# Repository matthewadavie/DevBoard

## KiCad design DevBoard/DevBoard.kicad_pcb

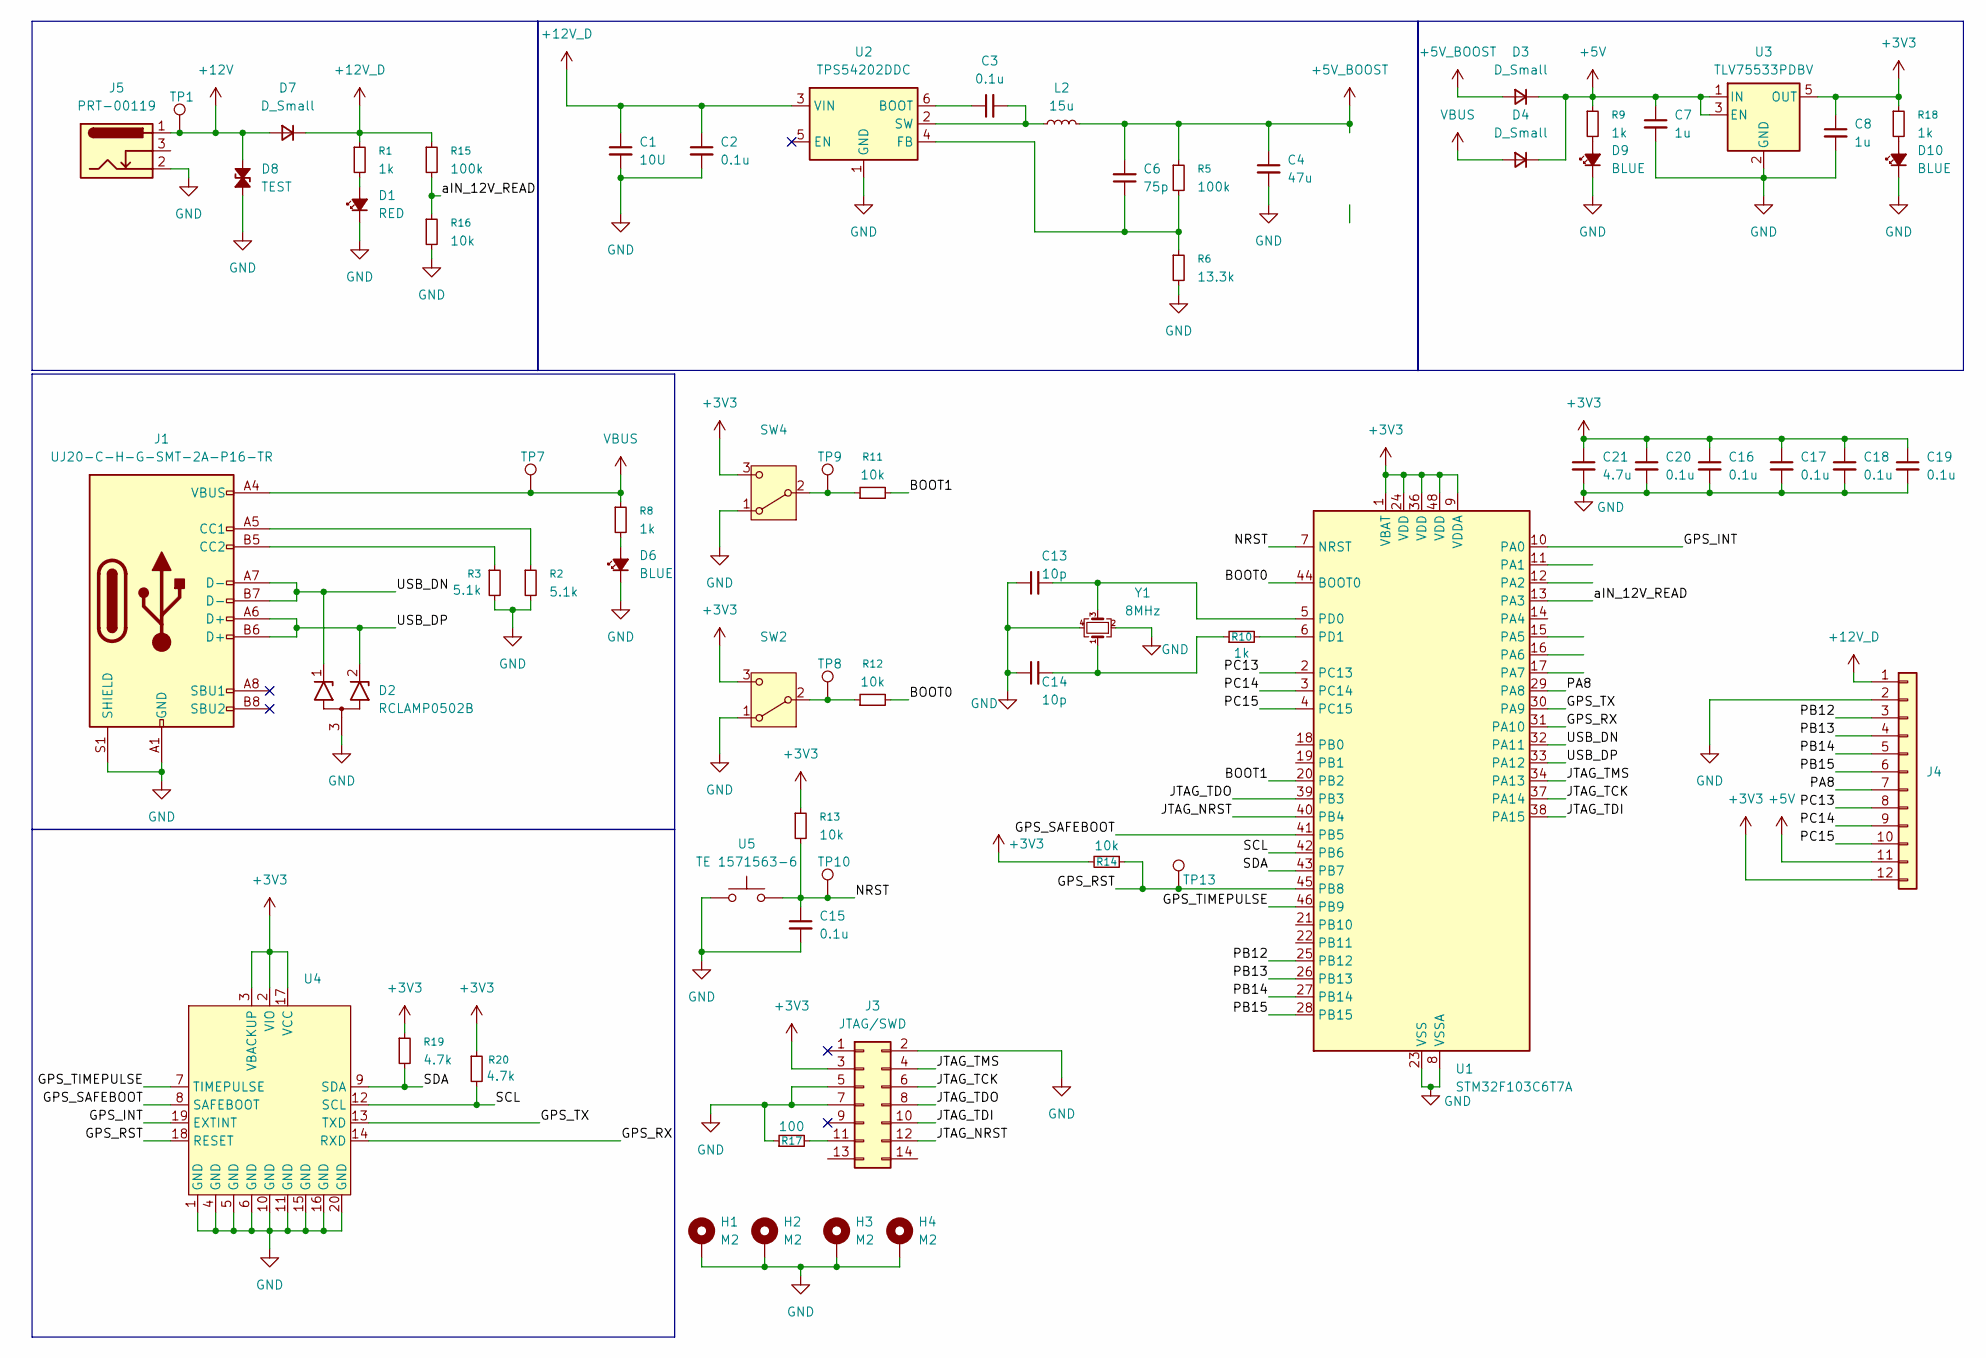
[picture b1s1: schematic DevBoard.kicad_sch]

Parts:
C1: 10U; C_0805_2012Metric_Pad1.18x1.45mm_HandSolder
C2, C3, C15, C16, C17, C18, C19, C20: 0.1u; C_0603_1608Metric_Pad1.08x0.95mm_HandSolder
C4: 47u; C_0805_2012Metric_Pad1.18x1.45mm_HandSolder
C6: 75p; C_0603_1608Metric_Pad1.08x0.95mm_HandSolder
C7, C8: 1u; C_0805_2012Metric_Pad1.18x1.45mm_HandSolder
C13, C14: 10p; C_0603_1608Metric_Pad1.08x0.95mm_HandSolder
C21: 4.7u; C_0805_2012Metric_Pad1.18x1.45mm_HandSolder
D1: RED; LED_0603_1608Metric_Pad1.05x0.95mm_HandSolder
D2: RCLAMP0502B; SOT-416
D3, D4, D7: D_Small; D_0805_2012Metric_Pad1.15x1.40mm_HandSolder
D6, D9, D10: BLUE; LED_0603_1608Metric_Pad1.05x0.95mm_HandSolder
D8: TEST
H1, H2, H3, H4: M2; MountingHole_2.2mm_M2_ISO7380_Pad_TopBottom
J1: UJ20-C-H-G-SMT-2A-P16-TR; MPN UJ20-C-H-G-SMT-2A-P16-TR; Mouser SPN 179-CHGSMT2AP16TR
J3: JTAG/SWD; PinHeader_2x07_P1.27mm_Vertical_SMD
J4: Conn_01x12; PinHeader_1x12_P2.54mm_Vertical
J5: PRT-00119; BarrelJack_3Pin_PJ202A; MPN PRT-00119; Mouser SPN 474-PRT-00119
L2: 15u; L_Coilcraft_XAL40; MPN XAL4040-153MEC; Mouser SPN 994-XAL4040-153MEC
R1, R8, R9, R18: 1k; R_0603_1608Metric_Pad0.98x0.95mm_HandSolder
R2, R3: 5.1k; R_0603_1608Metric_Pad0.98x0.95mm_HandSolder
R5, R15: 100k; R_0603_1608Metric_Pad0.98x0.95mm_HandSolder
R6: 13.3k; R_0603_1608Metric_Pad0.98x0.95mm_HandSolder
R10: 1k; R_0402_1005Metric_Pad0.72x0.64mm_HandSolder
R11, R12, R13, R14, R16: 10k; R_0603_1608Metric_Pad0.98x0.95mm_HandSolder
R17: 100; R_0603_1608Metric_Pad0.98x0.95mm_HandSolder
R19, R20: 4.7k; R_0603_1608Metric_Pad0.98x0.95mm_HandSolder
SW2, SW4: SLW-88229-2-SMT-TR; MPN SLW-88229-2-SMT-TR; Mouser SPN 179-SLW-88229-2SMTTR
TP1, TP7, TP8, TP9, TP10, TP13: TestPoint; TestPoint_Pad_D1.0mm
U1: STM32F103C6T7A; LQFP-48_7x7mm_P0.5mm; MPN STM32F103C6T7A; Mouser SPN 511-STM32F103C6T7A
U2: TPS54202DDC; SOT-23-6
U3: TLV75533PDBV; SOT-23-5
U4: SAM-M10Q
U5: TE 1571563-6; 506-1571563-6; MPN 1571563-6; Mouser SPN 506-1571563-6
Y1: 8MHz; Crystal_FC3BA; MPN FC3BAEBDI8.0-T1; Mouser SPN 815-FC3BAEBDI8.0-T1

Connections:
+3V3: C8.1, C16.1, C17.1, C18.1, C19.1, C20.1, C21.1, J3.3, J4.12, R13.1, R14.2, R18.1, R19.1, R20.1, SW2.3 (C), SW4.3 (C), U1.1 (VBAT), U1.9 (VDDA), U1.24 (VDD), U1.36 (VDD), U1.48 (VDD), U3.5 (OUT), U4.2 (VIO), U4.3 (VBACKUP), U4.17 (VCC); also elsewhere on the board
+5V: C7.1, D3.1 (K), D4.1 (K), J4.11, R9.1, U3.1 (IN), U3.3 (EN)
+5V_BOOST: C4.1, C6.2, D3.2 (A), L2.2, R5.1
+12V: D7.2 (A), D8.2 (A2), J5.1, TP1.1
+12V_D: C1.1, C2.1, D7.1 (K), J4.1, R1.1, R15.1, U2.3 (VIN)
/BOOT0: R12.2, U1.44 (BOOT0)
/BOOT1: R11.2, U1.20 (PB2)
/GPS_INT: U1.10 (PA0), U4.19 (EXTINT)
/GPS_RST: R14.1, TP13.1, U1.45 (PB8), U4.18 (RESET)
/GPS_RX: U1.31 (PA10), U4.14 (RXD)
/GPS_SAFEBOOT: U1.41 (PB5), U4.8 (SAFEBOOT)
/GPS_TIMEPULSE: U1.46 (PB9), U4.7 (TIMEPULSE)
/GPS_TX: U1.30 (PA9), U4.13 (TXD)
/JTAG_NRST: J3.12, U1.40 (PB4)
/JTAG_TCK: J3.6, U1.37 (PA14)
/JTAG_TDI: J3.10, U1.38 (PA15)
/JTAG_TDO: J3.8, U1.39 (PB3)
/JTAG_TMS: J3.4, U1.34 (PA13)
/NRST: C15.1, R13.2, TP10.1, U1.7 (NRST), U5.2
/PA8: J4.7, U1.29 (PA8)
/PB12: J4.3, U1.25 (PB12)
/PB13: J4.4, U1.26 (PB13)
/PB14: J4.5, U1.27 (PB14)
/PB15: J4.6, U1.28 (PB15)
/PC13: J4.8, U1.2 (PC13)
/PC14: J4.9, U1.3 (PC14)
/PC15: J4.10, U1.4 (PC15)
/SCL: R20.2, U1.42 (PB6), U4.12 (SCL)
/SDA: R19.2, U1.43 (PB7), U4.9 (SDA)
/USB_DN: D2.1 (K1), J1.A7 (D-), J1.B7 (D-), U1.32 (PA11)
/USB_DP: D2.2 (K2), J1.A6 (D+), J1.B6 (D+), U1.33 (PA12)
/aIN_12V_READ: R15.2, R16.1, U1.13 (PA3)
GND: C1.2, C2.2, C4.2, C7.2, C8.2, C13.1, C14.1, C15.2, C16.2, C17.2, C18.2, C19.2, C20.2, C21.2, D1.1 (K), D2.3 (A), D6.1 (K), D8.1 (A1), D9.1 (K), D10.1 (K), H1.1, H2.1, H3.1, H4.1, J1.A1 (GND), J1.A12 (GND), J1.B1 (GND), J1.B12 (GND), J1.S1 (SHIELD), J3.2, J3.5, J3.7, J4.2, J5.2, R2.2, R3.2, R6.2, R16.2, R17.1, SW2.1 (A), SW4.1 (A), U1.8 (VSSA), U1.23 (VSS), U1.35 (VSS), U1.47 (VSS), U2.1 (GND), U3.2 (GND), U4.1 (GND), U4.4 (GND), U4.5 (GND), U4.6 (GND), U4.10 (GND), U4.11 (GND), U4.15 (GND), U4.16 (GND), U4.20 (GND), U5.1, Y1.2, Y1.4
unnamed: C14.2, R10.1, Y1.1
unnamed: D1.2 (A), R1.2
unnamed: D6.2 (A), R8.2
unnamed: D9.2 (A), R9.2
unnamed: D10.2 (A), R18.2
unnamed: J1.A5 (CC1), R2.1
unnamed: J1.B5 (CC2), R3.1
unnamed: J3.11, R17.2
unnamed: R12.1, SW2.2 (B), TP8.1
unnamed: R11.1, SW4.2 (B), TP9.1
unnamed: C13.2, U1.5 (PD0), Y1.3
unnamed: R10.2, U1.6 (PD1)
unnamed: C3.1, U2.6 (BOOT)
unnamed: C6.1, R5.2, R6.1, U2.4 (FB)
unnamed: C3.2, L2.1, U2.2 (SW)
VBUS: D4.2 (A), J1.A4 (VBUS), J1.A9 (VBUS), J1.B4 (VBUS), J1.B9 (VBUS), R8.1, TP7.1

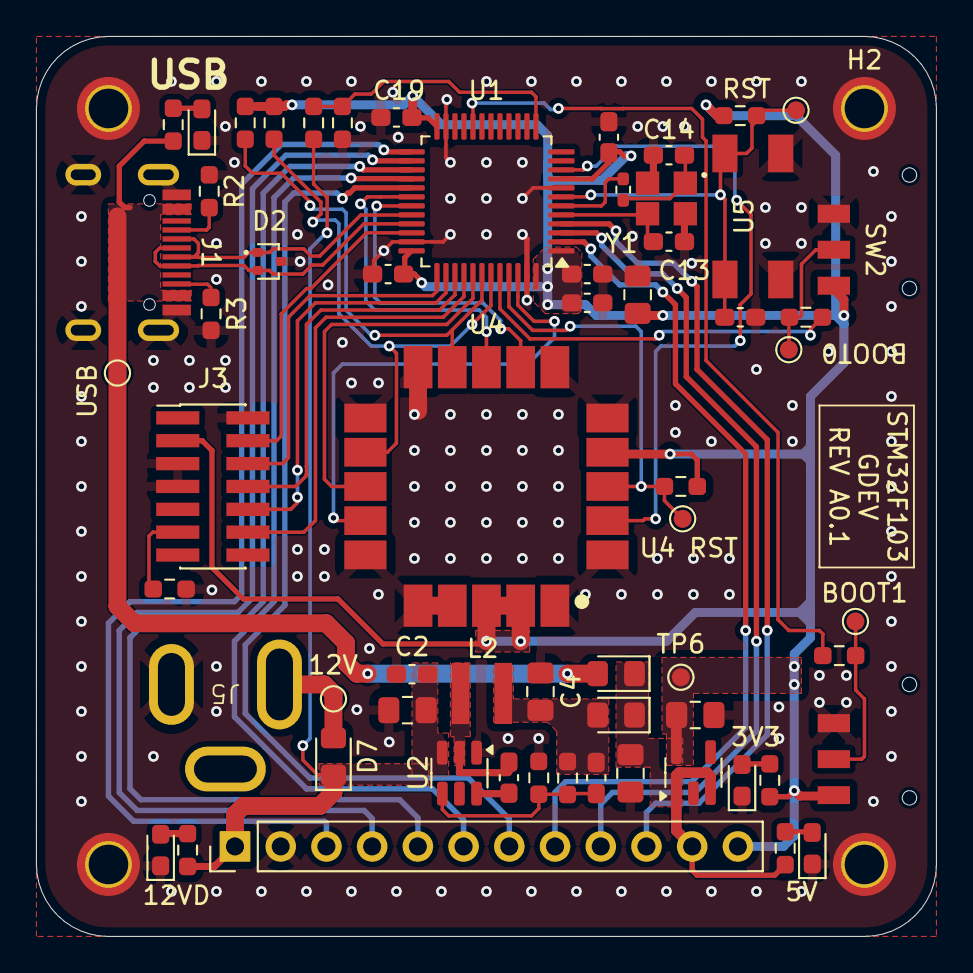
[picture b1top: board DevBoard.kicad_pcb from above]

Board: 4 copper layers, 50.0 x 50.0 mm, 66 parts (0 on the bottom side), 49 nets.

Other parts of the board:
TP6: TestPoint; TestPoint_Pad_D1.0mm

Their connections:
+3V3: TP6.1; also elsewhere on the board

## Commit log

2026-01-31 Initial layout/schematic
2026-02-02 Updates to DRC/schematic/layout. Layout to be redone.
2026-02-04 A0.1 layout (not happy, will be redone again)
